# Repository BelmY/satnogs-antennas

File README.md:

# SatNOGS Antennas

Antennas for SatNOGS project

More information can be found in our [documentation](https://satnogs.org/documentation/hardware/).

## What's here?

### Helical antenna designs

* `Helical/UHC lhcp-version_1` is version 1 of our Helical antenna design.  It's
  a left-hand circularly polarized (LHCP) antenna, and requires only
  3D-printed parts (no CNC milling or laser-cutting required).

* `Helical/UHF-434-8-version_4` is version 4 of our Helical antenna design, an
  8-turn Helix that can be made in either left- or right-hand
  circularly polarized (RHCP) configurations.  It requires a laser cutter or
  water jet cutter for the plexiglass/polycarbonate supports, but is
  more rigid than version 1.

* `Helical/UHF-435-8-version_5` is version 5 of the Helical antenna
  design; it comes in RHCP configuration.  The supports are made from
  aluminum, and will require a drill press.

## License

&copy; 2014-2015 [Libre Space Foundation](http://librespacefoundation.org).

Licensed under the [CERN OHLv1.2](LICENSE).

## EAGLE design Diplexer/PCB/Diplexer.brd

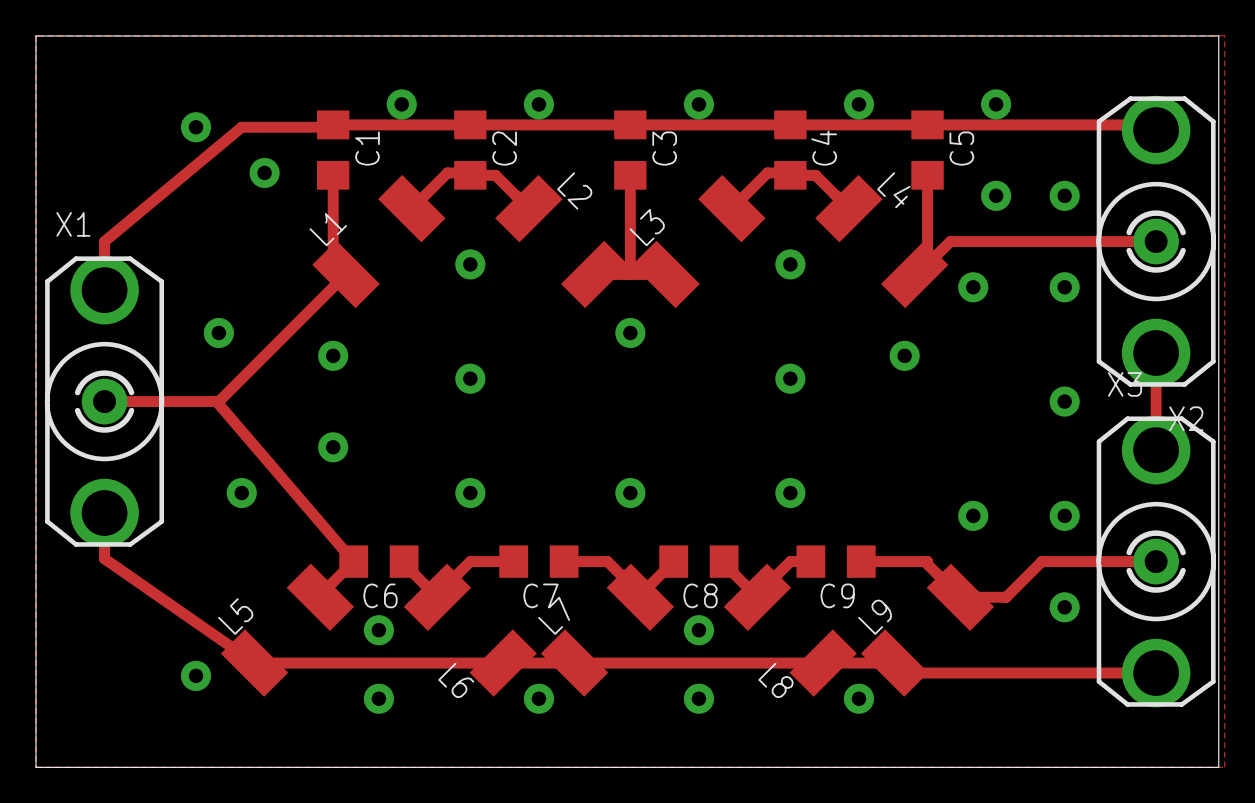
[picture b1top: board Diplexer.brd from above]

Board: 2 copper layers, 65.7 x 40.6 mm, 21 parts (0 on the bottom side), 10 nets.

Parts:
C1, C5: 20p; C1206
C2, C3, C4: 30p; C1206
C6, C7, C8, C9: 9.4p; C1206
L1, L2, L3, L4: 36.61n; AIR_CORE_INDUCTOR
L5, L9: 15.16n; AIR_CORE_INDUCTOR
L6, L7, L8: 8.63n; AIR_CORE_INDUCTOR
X1, X2, X3: SMASMA; SMA

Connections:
GND: C1.1, C2.1, C3.1, C4.1, C5.1, L5.1, L6.1, L7.1, L8.1, L9.1, X1.2, X1.4, X2.2, X2.4, X3.2, X3.4
unnamed: C1.2, C6.2, L1.1, L5.2, X1.1
unnamed: C2.2, L1.2, L2.1
unnamed: C3.2, L2.2, L3.1
unnamed: C4.2, L3.2, L4.1
unnamed: C5.2, L4.2, X2.1
unnamed: C6.1, C7.2, L6.2
unnamed: C7.1, C8.2, L7.2
unnamed: C8.1, C9.2, L8.2
unnamed: C9.1, L9.2, X3.1

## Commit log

2014-04-13 Yagi element to mast mounting bracket
2014-04-13 Code clean up and new stls
2014-04-13 T-connector and refactored code for axis mount
2014-04-13 STL files of the tracking box system.
2014-04-15 made axis hole smaller and added holes for screws
2014-04-15 added box axis bushing file
2014-04-15 corrected axis bushing file to fit in box
2014-04-15 enlarged bushing and axis large axis diameter
2014-04-20 Tripod and yagi antenna holders
2014-04-22 Add assemply blender filles .gitignore and how to blend and pics
2014-04-23 added antenna axs joint.stl file
2014-05-10 New antenna axis mount
2014-05-10 Manifold fix
2014-05-10 Turnstile antenna mount
2014-08-20 v0.1 source initial and final commit
2014-08-20 v0.2 source initial commit
2014-08-20 LNA housing
2014-08-20 Fixing spelling
2014-09-24 Ground Station Tracking v2
2014-09-24 Update BOM with links to STLs.
2014-09-24 Update Antenna directories.
2014-09-24 Updated BOM.
2014-09-28 New Helical antenna UHF lhcp.
2014-09-28 Add BOM of helical antenna UHF-lhcp.
2014-09-29 Add v2 of Tripod.
2014-10-04 Add axis_bushing source file.
2014-10-04 Add Axis Gear Spacer for v2.
2014-10-22 Add BOM for tripod v2
2014-10-24 Radome v1 added.
2014-10-26 Add all files for the diplexer schematic and pcb design
2014-10-27 Add Diplexer BOM.
2014-10-27 Update STL for Radome.
2014-10-27 Add Radome BOM.
2014-10-28 Update trakcer BOM.
2015-01-09 Add pockets for nuts at the axis_side part and update the stl file to
2015-01-18 Adding new yagi VHF v2
2015-01-18 Adding pdfs of Yagi VHF v2.
2015-02-05 New VHF v3 6element design.
2015-02-05 New UHF v1 10 elements design.
2015-03-08 Optimizing sensor holder for printability.
2015-03-08 Add source file and binary for homing ring.
2015-03-08 Modified axis gear ring in order to reduce friction.
2015-03-11 Change gitignore to ignore freecad backup files
2015-03-11 Add 3D printed cable hook to manage cables inside box
2015-03-11 Modify axis_bushing to be able to hold 2 ISO 3601 Size:026 o-rings on each side (for the 32mm diameter tube) to prevent water from licking in the box.
2015-04-14 Cleanup antennas repository.
2015-04-24 Update README with license notice
2015-04-27 Update documentation link
2015-05-08 First release of 4:1 balun PCB
2015-05-08 four-to-one-balun: Center schematic to page frame
2015-05-09 Fix connector obstruction to antenna elements
2015-06-13 nec2: GNU Octave antenna wavelength calculator
2015-06-13 nec2: Numerical electromagnetics code model for 6-element Yagi-Uda antenna
2015-06-13 nec2: Use V, H and total axis gain
2015-06-13 nec2: Fix phi range
2015-06-13 nec2: Add SatNOGS 6-element Yagi-Uda NEC2 output
2015-06-13 nec2: Radiation pattern, gain and SWR charts for SatNOGS 6-element Yagi-Uda antenna
2015-06-13 nec2: Code refactoring, print actual size, scale to tune at 145MHz
2015-06-13 nec2: Update cards with new wavelength and re-run simulation
2015-06-13 nec2: Update radiation pattern, SWR and gain charts
2015-06-13 nec2: Calculate sizes and distances for 8mm diameter elements
2015-06-13 nec2: Update cards with new wavelength after element diameter change
2015-06-13 nec2: Remove simulation output from repository
2015-06-13 nec2: Update radiation pattern and gain/SWR/impedance plots with results from new simulation
2015-06-13 Fix 6-element Yagi/Uda sloped elements
2015-06-13 nec2: Add GNU octave calculator and NEC2 file for 10-element Yagi/Uda UHF antenna
2015-06-13 nec2: Add GNU octave calculator and NEC2 file for 11-element Yagi/Uda UHF antenna
2015-06-13 Rename directory 'nec2' to 'NEC'
2015-09-01 Remove 'Balun' directory; four-to-one-balun has its own repository now at https://github.com/satnogs/four-to-one-balun/
2016-02-23 New directory for UHF Helical 434-8
2016-02-23 Designs for UHF Helical antenna in 434 MHz - 8 turns
2016-12-06 Folder for 435-8 helical design.
2017-10-15 Begin documenting what antenna versions are in the repo
2017-11-03 Add explanation of what's in this directory
    Source: https://satnogs.dozuki.com/Guide/Helical+Antenna+v4/11
2017-11-13 Incorporate versions in directory names
2017-11-13 Update README files with version names and links to assembly
2020-02-16 Add Libre Space Foundation Contribution Guide
2020-02-17 Fix license file to match original text version
